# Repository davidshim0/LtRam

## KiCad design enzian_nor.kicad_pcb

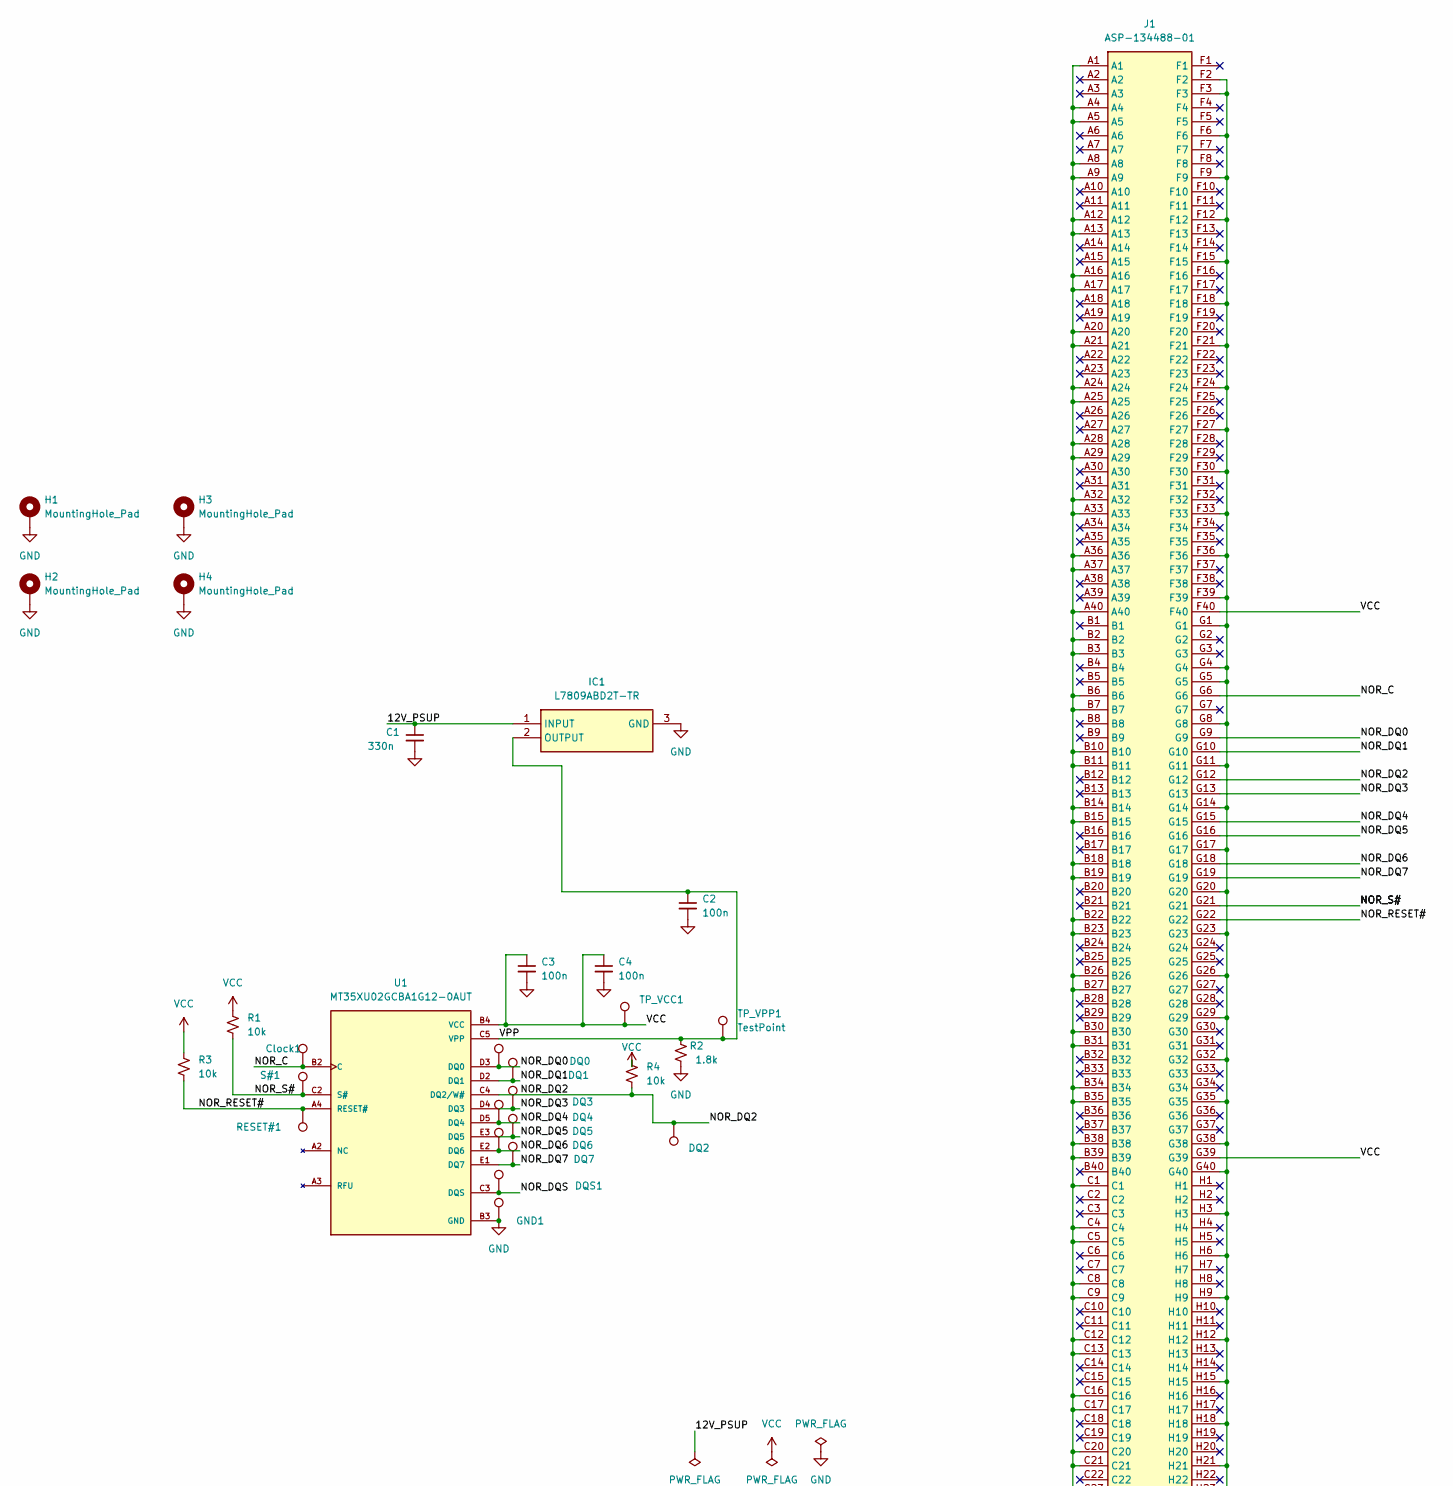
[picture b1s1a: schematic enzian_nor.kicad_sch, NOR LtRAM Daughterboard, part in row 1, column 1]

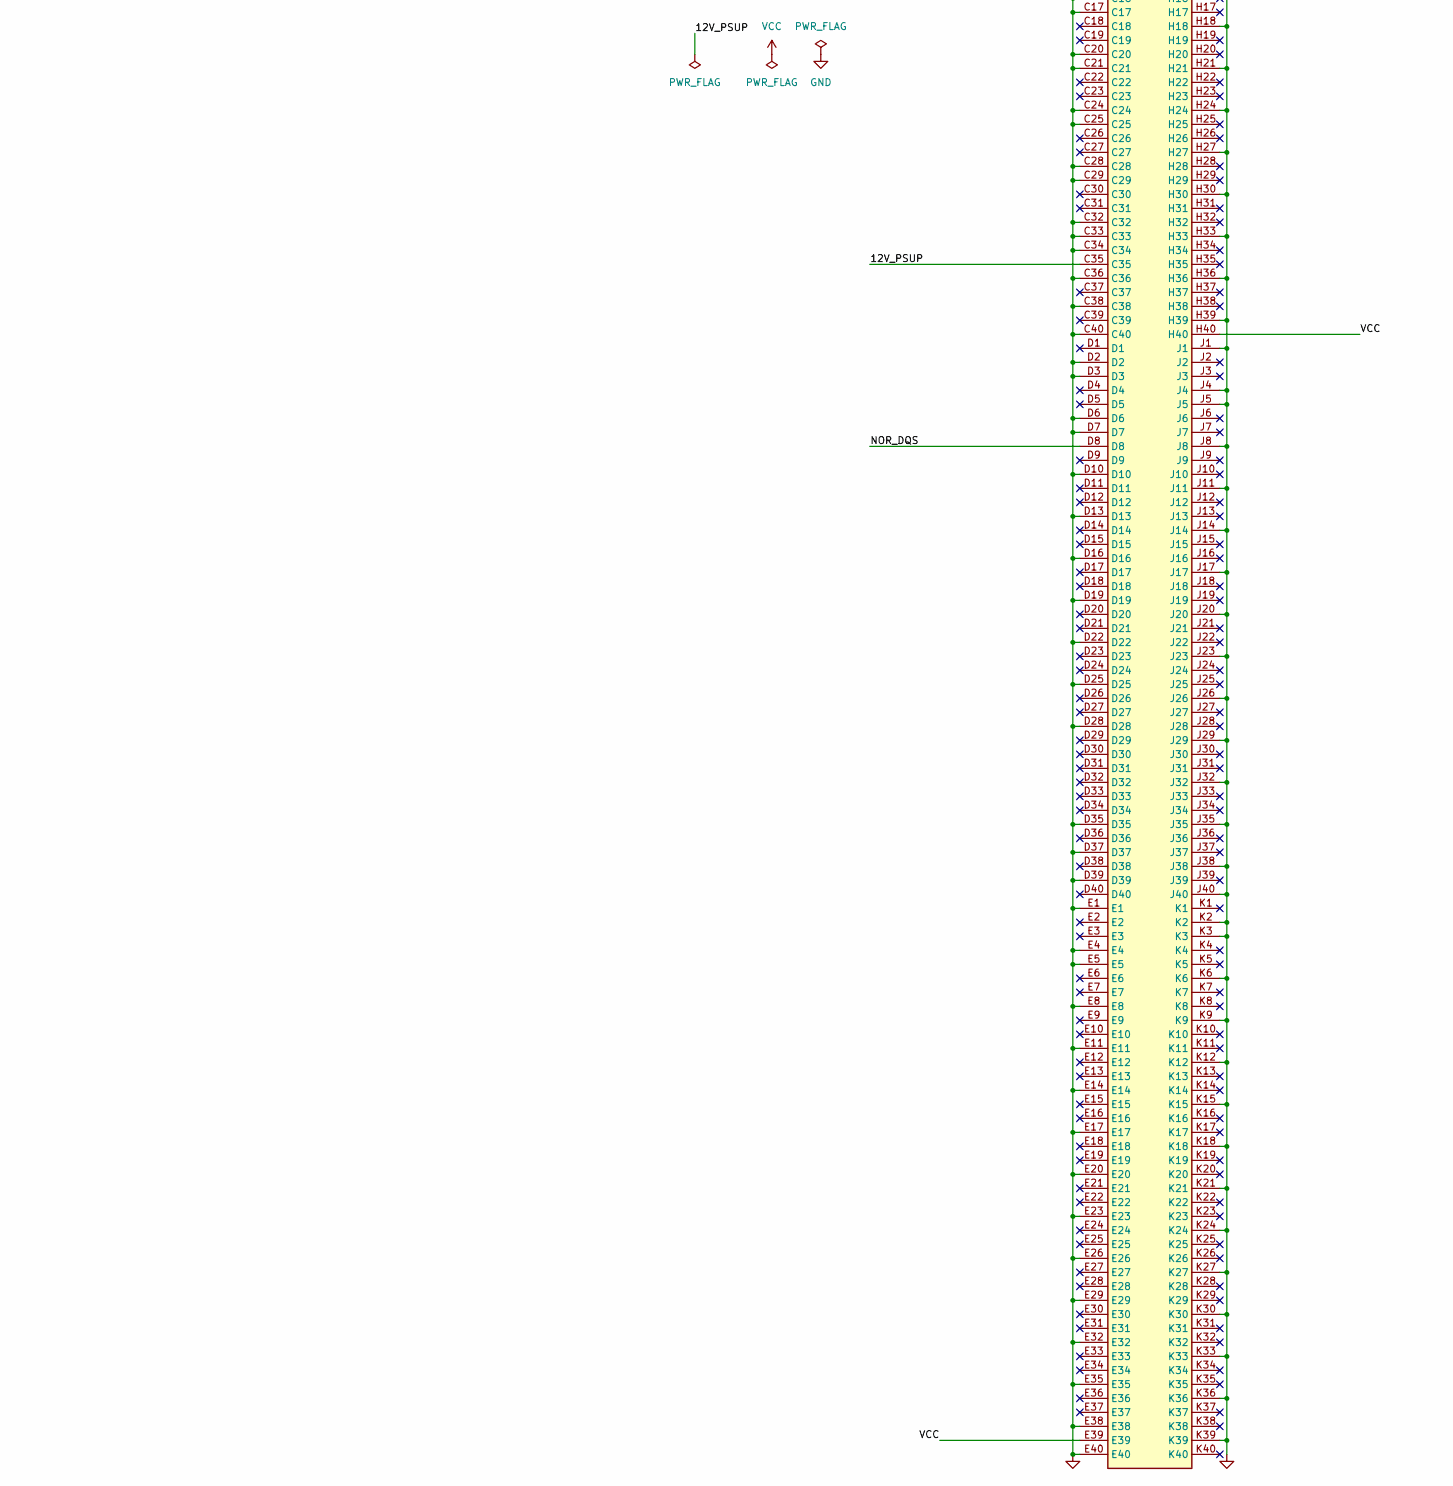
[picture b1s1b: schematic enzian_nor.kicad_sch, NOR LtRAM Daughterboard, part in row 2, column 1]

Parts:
C1: 330n; C_0805_2012Metric
C2, C3, C4: 100n; C_0805_2012Metric
Clock1: TestPoint; TestPoint_Pad_D1.0mm
DQ0, DQ1, DQ2, DQ3, DQ4, DQ5, DQ6, DQ7: TestPoint; TestPoint_Pad_D1.0mm
DQS1: TestPoint; TestPoint_Pad_D1.0mm
GND1: TestPoint; TestPoint_Loop_D2.50mm_Drill1.0mm
H1, H2, H3, H4: MountingHole_Pad; MountingHole_3.2mm_M3_Pad_Via
IC1: L7809ABD2T-TR; STB30NM60ND; Manufacturer_Part_Number L7809ABD2T-TR; Mouser Part Number 511-L7809ABD2T-TR
J1: ASP-134488-01; ASP13448801; Mouser Part Number 200-ASP-134488-01
R1, R3, R4: 10k; R_0805_2012Metric
R2: 1.8k; R_0805_2012Metric
RESET#1: TestPoint; TestPoint_Pad_D1.0mm
S#1: TestPoint; TestPoint_Pad_D1.0mm
TP_VCC1: VCC; TestPoint_Pad_D1.0mm
TP_VPP1: TestPoint; TestPoint_Pad_D1.0mm
U1: MT35XU02GCBA1G12-0AUT; BGA24C100P5X5_800X600X120N; PARTREV A 04/18; DigiKey_Part_Number MT35XU02GCBA1G12-0AUT-ND

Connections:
/12V_PSUP: C1.1, IC1.1 (INPUT), J1.C35
/NOR_C: Clock1.1, J1.G6, U1.B2 (C)
/NOR_DQ0: DQ0.1, J1.G9, U1.D3 (DQ0)
/NOR_DQ1: DQ1.1, J1.G10, U1.D2 (DQ1)
/NOR_DQ2: DQ2.1, J1.G12, R4.2, U1.C4 (DQ2/W#)
/NOR_DQ3: DQ3.1, J1.G13, U1.D4 (DQ3)
/NOR_DQ4: DQ4.1, J1.G15, U1.D5 (DQ4)
/NOR_DQ5: DQ5.1, J1.G16, U1.E3 (DQ5)
/NOR_DQ6: DQ6.1, J1.G18, U1.E2 (DQ6)
/NOR_DQ7: DQ7.1, J1.G19, U1.E1 (DQ7)
/NOR_DQS: DQS1.1, J1.D8, U1.C3 (DQS)
/NOR_RESET#: J1.G22, R3.2, RESET#1.1, U1.A4 (RESET#)
/NOR_S#: J1.G21, R1.2, S#1.1, U1.C2 (S#)
/VPP: C2.1, IC1.2 (OUTPUT), R2.1, TP_VPP1.1, U1.C5 (VPP)
GND: C1.2, C2.2, C3.2, C4.2, GND1.1, H1.1, H2.1, H3.1, H4.1, IC1.3 (GND), J1.A1, J1.A4, J1.A5, J1.A8, J1.A9, J1.A12, J1.A13, J1.A16, J1.A17, J1.A20, J1.A21, J1.A24, J1.A25, J1.A28, J1.A29, J1.A32, J1.A33, J1.A36, J1.A37, J1.A40, J1.B2, J1.B3, J1.B6, J1.B7, J1.B10, J1.B11, J1.B14, J1.B15, J1.B18, J1.B19, J1.B22, J1.B23, J1.B26, J1.B27, J1.B30, J1.B31, J1.B34, J1.B35, J1.B38, J1.B39, J1.C1, J1.C4, J1.C5, J1.C8, J1.C9, J1.C12, J1.C13, J1.C16, J1.C17, J1.C20, J1.C21, J1.C24, J1.C25, J1.C28, J1.C29, J1.C32, J1.C33, J1.C34, J1.C36, J1.C38, J1.C40, J1.D2, J1.D3, J1.D6, J1.D7, J1.D10, J1.D13, J1.D16, J1.D19, J1.D22, J1.D25, J1.D28, J1.D35, J1.D37, J1.D39, J1.E1, J1.E4, J1.E5, J1.E8, J1.E11, J1.E14, J1.E17, J1.E20, J1.E23, J1.E26, J1.E29, J1.E32, J1.E35, J1.E38, J1.E40, J1.F2, J1.F3, J1.F6, J1.F9, J1.F12, J1.F15, J1.F18, J1.F21, J1.F24, J1.F27, J1.F30, J1.F33, J1.F36, J1.F39, J1.G1, J1.G4, J1.G5, J1.G8, J1.G11, J1.G14, J1.G17, J1.G20, J1.G23, J1.G26, J1.G29, J1.G32, J1.G35, J1.G38, J1.G40, J1.H3, J1.H6, J1.H9, J1.H12, J1.H15, J1.H18, J1.H21, J1.H24, J1.H27, J1.H30, J1.H33, J1.H36, J1.H39, J1.J1, J1.J4, J1.J5, J1.J8, J1.J11, J1.J14, J1.J17, J1.J20, J1.J23, J1.J26, J1.J29, J1.J32, J1.J35, J1.J38, J1.J40, J1.K2, J1.K3, J1.K6, J1.K9, J1.K12, J1.K15, J1.K18, J1.K21, J1.K24, J1.K27, J1.K30, J1.K33, J1.K36, J1.K39, R2.2, U1.B3 (GND), U1.C1 (GND), U1.E5 (GND)
VCC: C3.1, C4.1, J1.E39, J1.F40, J1.G39, J1.H40, R1.1, R3.1, R4.1, TP_VCC1.1, U1.B4 (VCC), U1.D1 (VCC), U1.E4 (VCC)

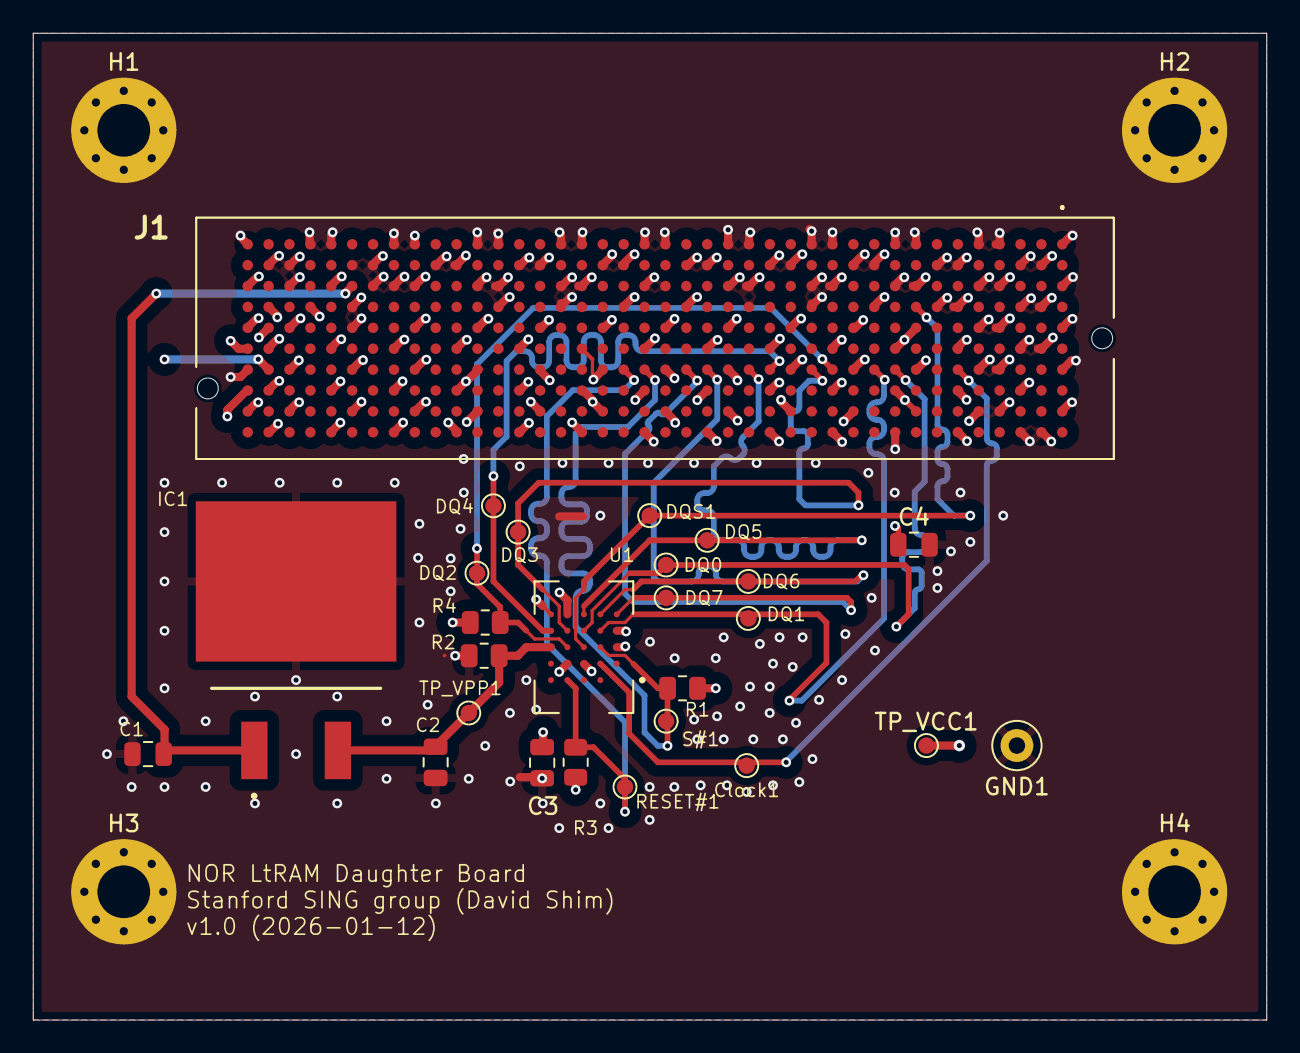
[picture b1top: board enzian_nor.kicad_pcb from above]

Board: 4 copper layers, 75.0 x 60.0 mm, 30 parts (0 on the bottom side), 16 nets.

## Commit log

2025-12-16 Place VPP capacitor closer to LDO
2025-12-16 Match constraints with example board
2025-12-17 Update vias to diagonal positions to match the enzian main board
2026-01-06 Change trace width to 0.35mm/0.5mm for control/power traces, and connected test pads
2026-01-06 Match trace lengths for all control signals (DQ0-7, C, S#)
2026-01-06 Pour coplanarground plane on the front copper
2026-01-06 Via stitching for the coplanar ground plane
2026-01-09 Revised length matching so meanders have 2x trace width between traces
2026-01-12 Add version number, mounting holes, and minor changes to via placement
2026-01-12 Update schematics along with the pcb design
2026-01-27 Applied Mark's suggestions
2026-02-03 Modified changes to print PCB
2026-02-18 Added all 1V8 power pins to schematic and PCB
